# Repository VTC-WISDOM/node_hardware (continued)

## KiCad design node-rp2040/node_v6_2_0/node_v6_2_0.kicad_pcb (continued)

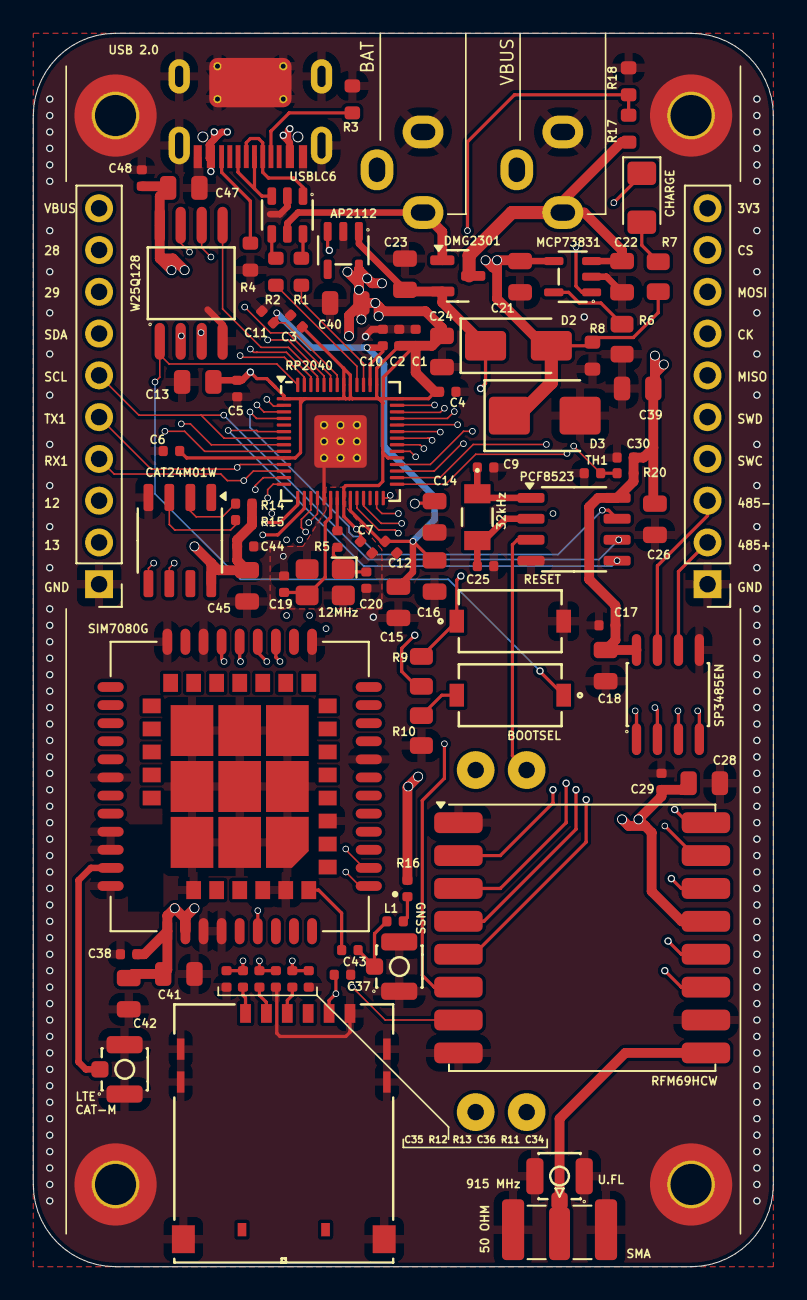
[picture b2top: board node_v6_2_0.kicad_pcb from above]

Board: 6 copper layers, 45.0 x 75.0 mm, 96 parts (1 on the bottom side), 77 nets.

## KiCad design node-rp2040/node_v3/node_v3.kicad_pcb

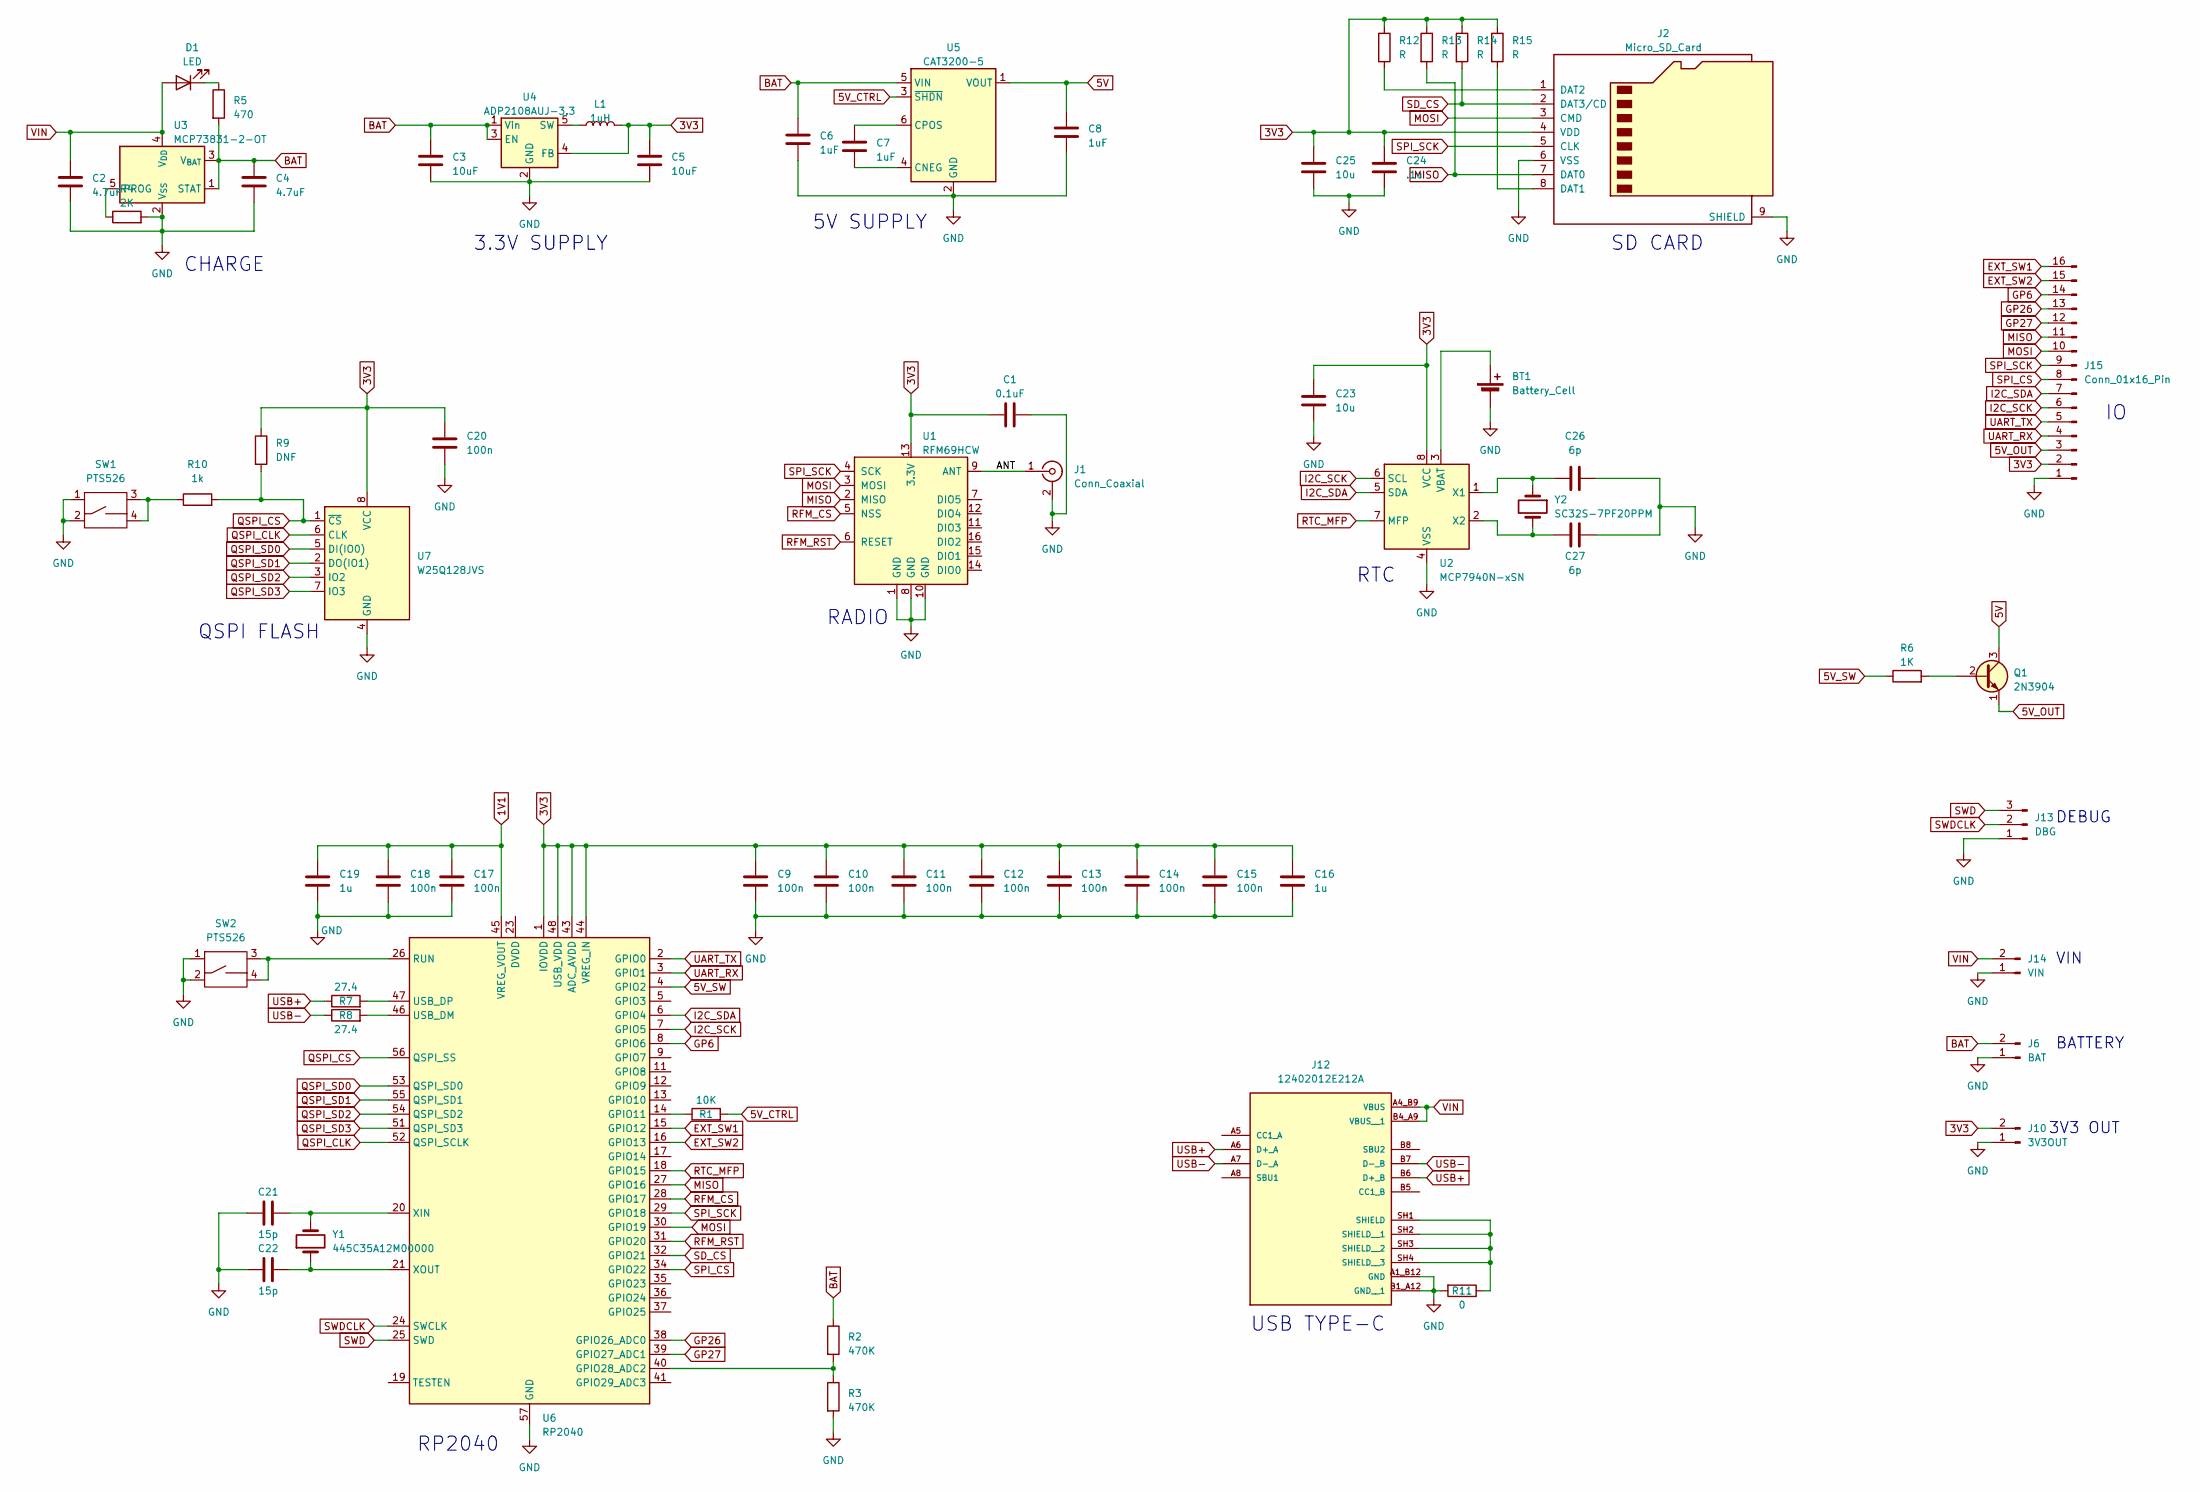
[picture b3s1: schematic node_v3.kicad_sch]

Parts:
BT1: Battery_Cell; BAT-HLD-001-THM_TEC
C1: 0.1uF; C_0402_1005Metric
C2, C4: 4.7uF; C_0805_2012Metric_Pad1.18x1.45mm_HandSolder
C3, C5: 10uF; C_0805_2012Metric_Pad1.18x1.45mm_HandSolder
C6, C7, C8: 1uF; C_0805_2012Metric_Pad1.18x1.45mm_HandSolder
C9, C10, C11, C12, C13, C14, C15, C17, C18, C20: 100n; C_0402_1005Metric_Pad0.74x0.62mm_HandSolder
C16, C19: 1u; C_0805_2012Metric_Pad1.18x1.45mm_HandSolder
C21, C22: 15p; C_0402_1005Metric_Pad0.74x0.62mm_HandSolder
C23, C25: 10u; C_0805_2012Metric_Pad1.18x1.45mm_HandSolder
C24: .1u; C_0402_1005Metric
C26, C27: 6p; C_0603_1608Metric_Pad1.08x0.95mm_HandSolder
D1: LED; LED_1206_3216Metric_Pad1.42x1.75mm_HandSolder
J1: Conn_Coaxial; SMA_Samtec_SMA-J-P-X-ST-EM1_EdgeMount
J2: Micro_SD_Card; microSD_HC_Molex_104031-0811
J6: BAT; PinHeader_1x02_P2.54mm_Vertical
J10: 3V3OUT; PinHeader_1x02_P2.54mm_Vertical
J12: 12402012E212A; AMPHENOL_12402012E212A; PARTREV 4
J13: DBG; PinHeader_1x03_P2.54mm_Vertical
J14: VIN; PinHeader_1x02_P2.54mm_Vertical
J15: Conn_01x16_Pin; PinHeader_1x16_P2.54mm_Vertical
L1: 1uH; L_1008_2520Metric_Pad1.43x2.20mm_HandSolder
Q1: 2N3904; SC-59_Handsoldering
R1: 10K; R_0805_2012Metric_Pad1.20x1.40mm_HandSolder
R2, R3: 470K; R_0805_2012Metric_Pad1.20x1.40mm_HandSolder
R4: 2K; R_0805_2012Metric_Pad1.20x1.40mm_HandSolder
R5: 470; R_0805_2012Metric_Pad1.20x1.40mm_HandSolder
R6: 1K; R_0805_2012Metric_Pad1.20x1.40mm_HandSolder
R7, R8: 27.4; R_0805_2012Metric_Pad1.20x1.40mm_HandSolder
R9: DNF; R_0805_2012Metric_Pad1.20x1.40mm_HandSolder
R10: 1k; R_0805_2012Metric_Pad1.20x1.40mm_HandSolder
R11: 0; R_0805_2012Metric_Pad1.20x1.40mm_HandSolder
R12, R13, R14, R15: R; R_0805_2012Metric_Pad1.20x1.40mm_HandSolder
SW1, SW2: PTS526
U1: RFM69HCW; HOPERF_RFM9XW_SMD
U2: MCP7940N-xSN; SOIC-8_3.9x4.9mm_P1.27mm
U3: MCP73831-2-OT; SOT-23-5
U4: ADP2108AUJ-3.3; TSOT-23-5
U5: CAT3200-5; SOT-23-6
U6: RP2040; QFN-56-1EP_7x7mm_P0.4mm_EP3.2x3.2mm
U7: W25Q128JVS; SOIC-8_5.23x5.23mm_P1.27mm
Y1: 445C35A12M00000; XTAL_M445
Y2: SC32S-7PF20PPM; SC-32S

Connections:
1V1: C17.1, C18.1, C19.1, U6.45 (VREG_VOUT)
3V3: C1.1, C5.1, C9.1, C10.1, C11.1, C12.1, C13.1, C14.1, C15.1, C16.1, C20.1, C23.1, C24.1, C25.1, J2.4 (VDD), J10.2, J15.2, L1.2, R9.1, R12.1, R13.1, R14.1, R15.1, U1.13 (3.3V), U2.8 (VCC), U4.4 (FB), U6.1 (IOVDD), U6.10 (IOVDD), U6.22 (IOVDD), U6.33 (IOVDD), U6.42 (IOVDD), U6.43 (ADC_AVDD), U6.44 (VREG_IN), U6.48 (USB_VDD), U6.49 (IOVDD), U7.8 (VCC)
5V: C8.1, Q1.3 (C), U5.1 (VOUT)
5V_CTRL: R1.2, U5.3 (~SHDN)
5V_OUT: J15.3, Q1.1 (E)
5V_SW: R6.1, U6.4 (GPIO2)
/ANT: J1.1 (In), U1.9 (ANT)
BAT: C3.1, C4.1, C6.1, J6.2, R2.1, R5.2, U3.1 (STAT), U3.3 (V_{BAT}), U4.1 (Vin), U4.3 (EN), U5.5 (VIN)
EXT_SW1: J15.16, U6.15 (GPIO12)
EXT_SW2: J15.15, U6.16 (GPIO13)
GP6: J15.14, U6.8 (GPIO6)
GP26: J15.13, U6.38 (GPIO26_ADC0)
GP27: J15.12, U6.39 (GPIO27_ADC1)
I2C_SCK: J15.6, U2.6 (SCL), U6.7 (GPIO5)
I2C_SDA: J15.7, U2.5 (SDA), U6.6 (GPIO4)
MISO: J2.7 (DAT0), J15.11, R13.2, U1.2 (MISO), U6.27 (GPIO16)
MOSI: J2.3 (CMD), J15.10, U1.3 (MOSI), U6.30 (GPIO19)
unnamed: D1.1 (K), R5.1
unnamed: J2.8 (DAT1), R15.2
unnamed: J2.1 (DAT2), R12.2
unnamed: J12.SH1 (SHIELD), J12.SH2 (SHIELD__1), J12.SH3 (SHIELD__2), J12.SH4 (SHIELD__3), R11.1
unnamed: Q1.2 (B), R6.2
unnamed: R10.1, SW1.3, SW1.4
unnamed: C26.1, U2.1 (X1), Y2.1
unnamed: C27.1, U2.2 (X2), Y2.2
unnamed: R4.1, U3.5 (PROG)
unnamed: L1.1, U4.5 (SW)
unnamed: C7.2, U5.4 (CNEG)
unnamed: C7.1, U5.6 (CPOS)
unnamed: U6.23 (DVDD), U6.50 (DVDD)
unnamed: R1.1, U6.14 (GPIO11)
unnamed: R2.2, R3.1, U6.40 (GPIO28_ADC2)
unnamed: SW2.3, SW2.4, U6.26 (RUN)
unnamed: R8.2, U6.46 (USB_DM)
unnamed: R7.2, U6.47 (USB_DP)
unnamed: C21.2, U6.20 (XIN), Y1.2
unnamed: C22.2, U6.21 (XOUT), Y1.1
QSPI_CLK: U6.52 (QSPI_SCLK), U7.6 (CLK)
QSPI_CS: R9.2, R10.2, U6.56 (QSPI_SS), U7.1 (~CS)
QSPI_SD0: U6.53 (QSPI_SD0), U7.5 (DI(IO0))
QSPI_SD1: U6.55 (QSPI_SD1), U7.2 (DO(IO1))
QSPI_SD2: U6.54 (QSPI_SD2), U7.3 (IO2)
QSPI_SD3: U6.51 (QSPI_SD3), U7.7 (IO3)
RFM_CS: U1.5 (NSS), U6.28 (GPIO17)
RFM_RST: U1.6 (RESET), U6.31 (GPIO20)
RTC_MFP: U2.7 (MFP), U6.18 (GPIO15)
SD_CS: J2.2 (DAT3/CD), R14.2, U6.32 (GPIO21)
SPI_CS: J15.8, U6.34 (GPIO22)
SPI_SCK: J2.5 (CLK), J15.9, U1.4 (SCK), U6.29 (GPIO18)
SWD: J13.3, U6.25 (SWD)
SWDCLK: J13.2, U6.24 (SWCLK)
UART_RX: J15.4, U6.3 (GPIO1)
UART_TX: J15.5, U6.2 (GPIO0)
USB+: J12.A6 (D+_A), J12.B6 (D+_B), R7.1
USB-: J12.A7 (D-_A), J12.B7 (D-_B), R8.1
VIN: C2.1, D1.2 (A), J12.A4_B9 (VBUS), J12.B4_A9 (VBUS__1), J14.2, U3.4 (V_{DD})

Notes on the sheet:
RTC
DEBUG
3V3 OUT
USB TYPE-C
3.3V SUPPLY
SD CARD
RADIO
RP2040
CHARGE
BATTERY
QSPI FLASH
VIN
5V SUPPLY

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
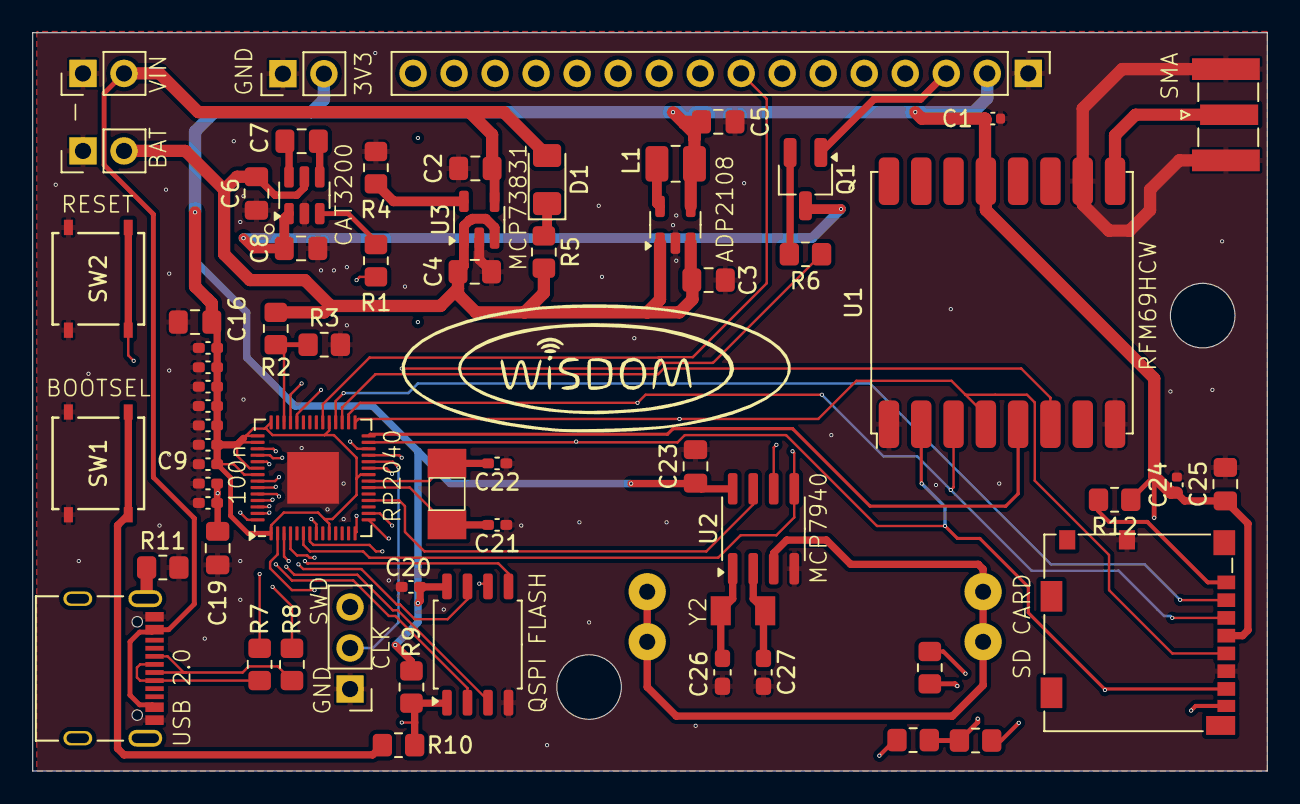
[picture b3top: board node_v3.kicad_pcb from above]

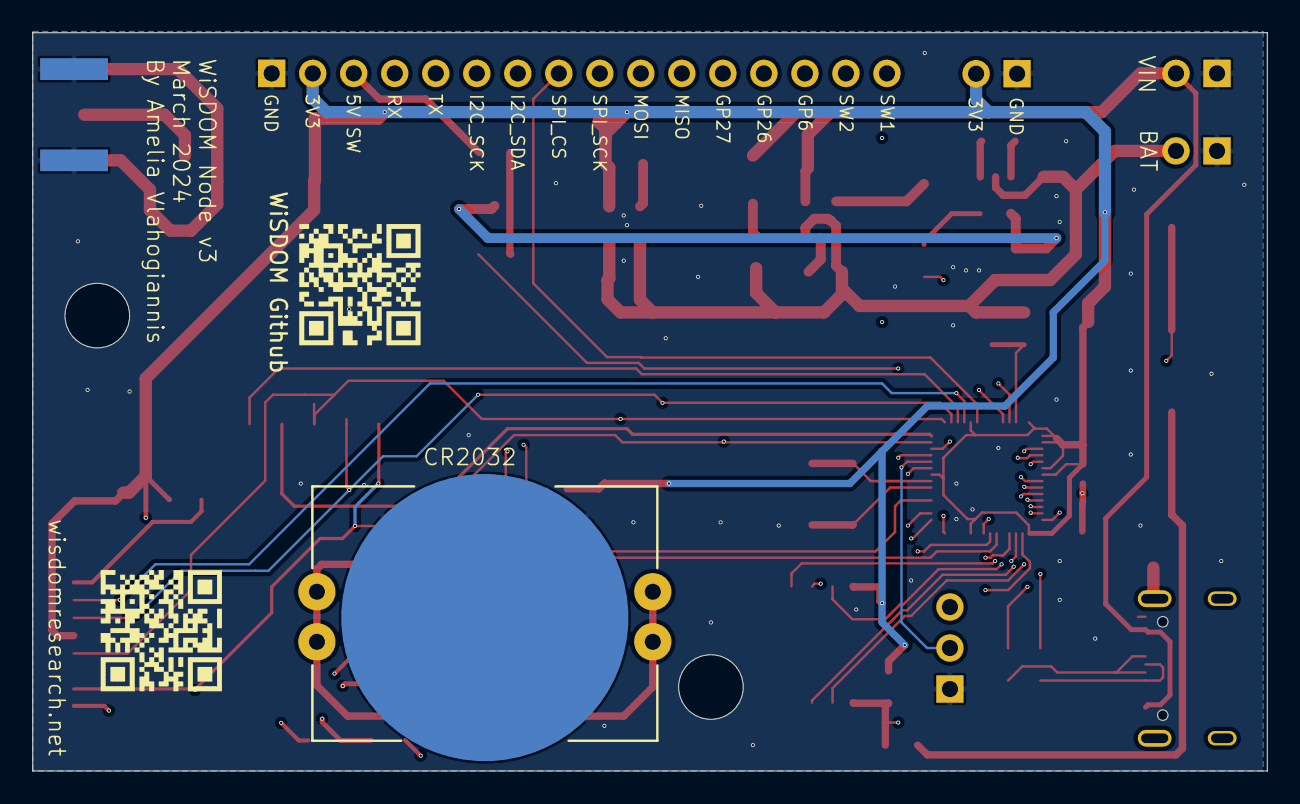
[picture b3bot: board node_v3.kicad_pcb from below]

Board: 4 copper layers, 76.5 x 45.7 mm, 67 parts (3 on the bottom side), 58 nets.

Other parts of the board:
LOGO: qrcode
LOGO#2: github_qr

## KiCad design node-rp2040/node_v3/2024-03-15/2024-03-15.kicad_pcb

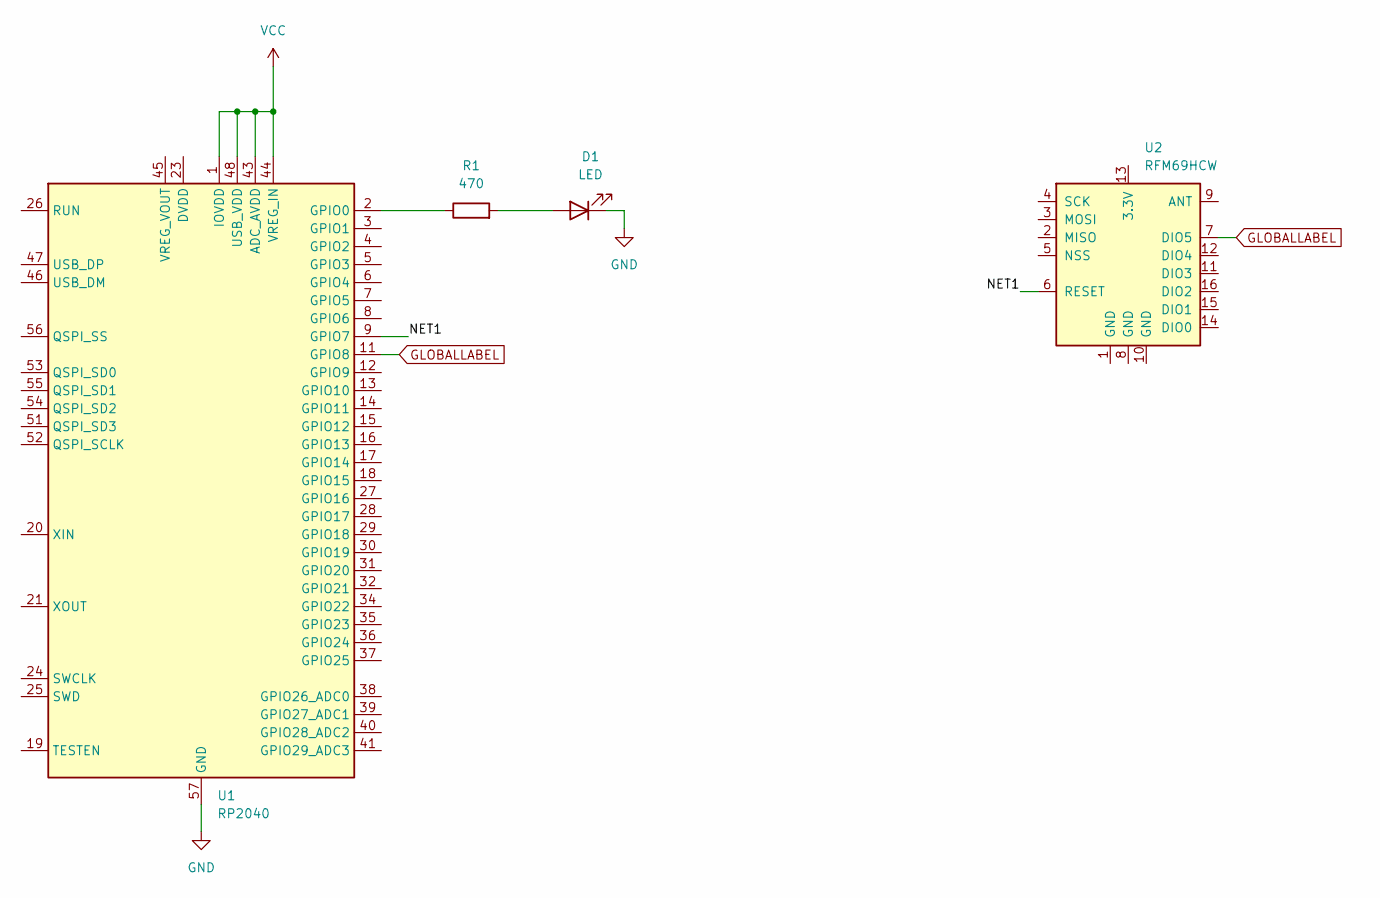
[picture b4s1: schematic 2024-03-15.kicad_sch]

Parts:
D1: LED; LED_D5.0mm
R1: 470; R_Axial_DIN0207_L6.3mm_D2.5mm_P7.62mm_Horizontal
U1: RP2040; QFN-56-1EP_7x7mm_P0.4mm_EP3.2x3.2mm
U2: RFM69HCW; HOPERF_RFM9XW_SMD

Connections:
/NET1: U1.9 (GPIO7), U2.6 (RESET)
GLOBALLABEL: U1.11 (GPIO8), U2.7 (DIO5)
GND: D1.1 (K), U1.57 (GND)
unnamed: D1.2 (A), R1.2
unnamed: U1.23 (DVDD), U1.50 (DVDD)
unnamed: R1.1, U1.2 (GPIO0)
VCC: U1.1 (IOVDD), U1.10 (IOVDD), U1.22 (IOVDD), U1.33 (IOVDD), U1.42 (IOVDD), U1.43 (ADC_AVDD), U1.44 (VREG_IN), U1.48 (USB_VDD), U1.49 (IOVDD)

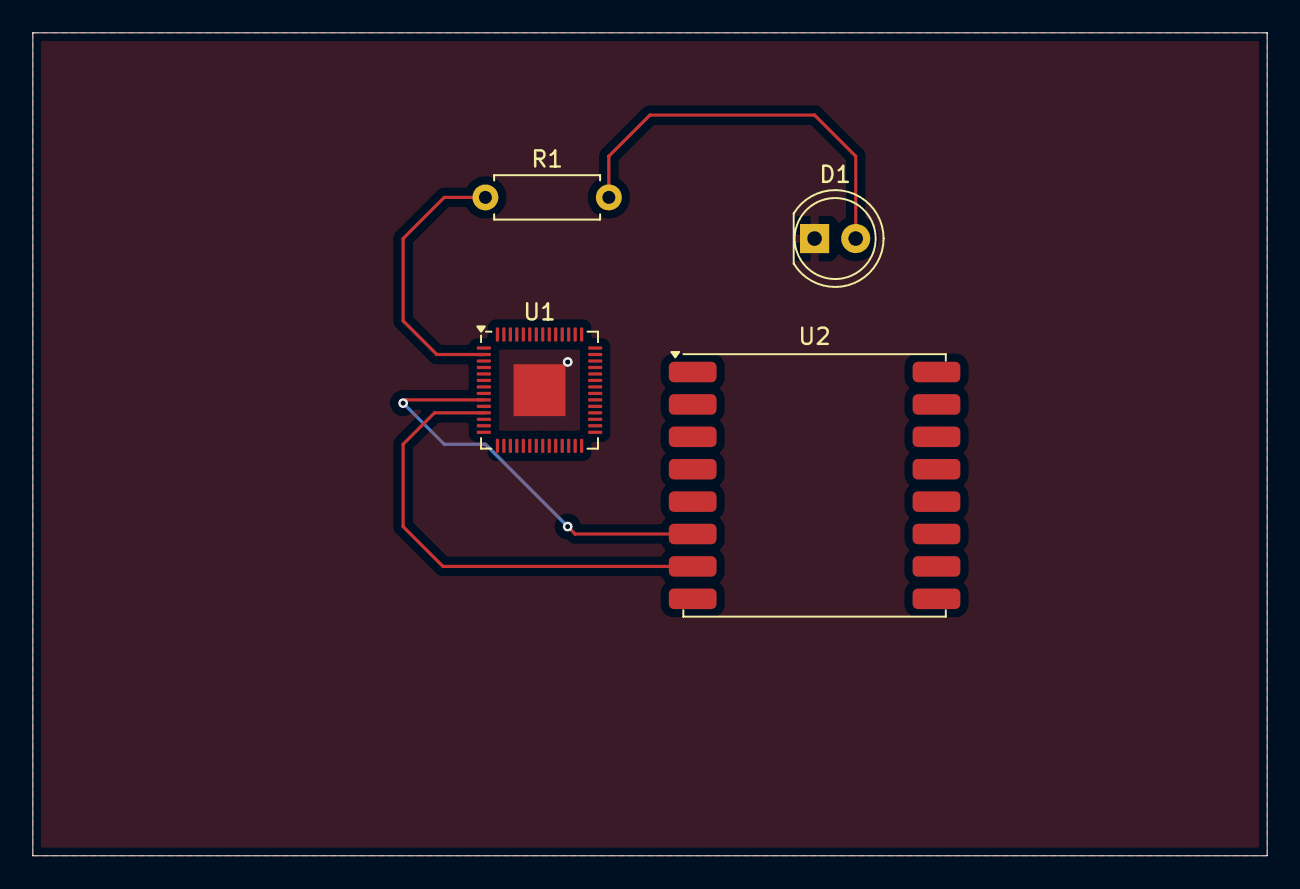
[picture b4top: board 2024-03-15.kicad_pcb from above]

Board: 2 copper layers, 76.2 x 50.8 mm, 4 parts (0 on the bottom side), 7 nets.

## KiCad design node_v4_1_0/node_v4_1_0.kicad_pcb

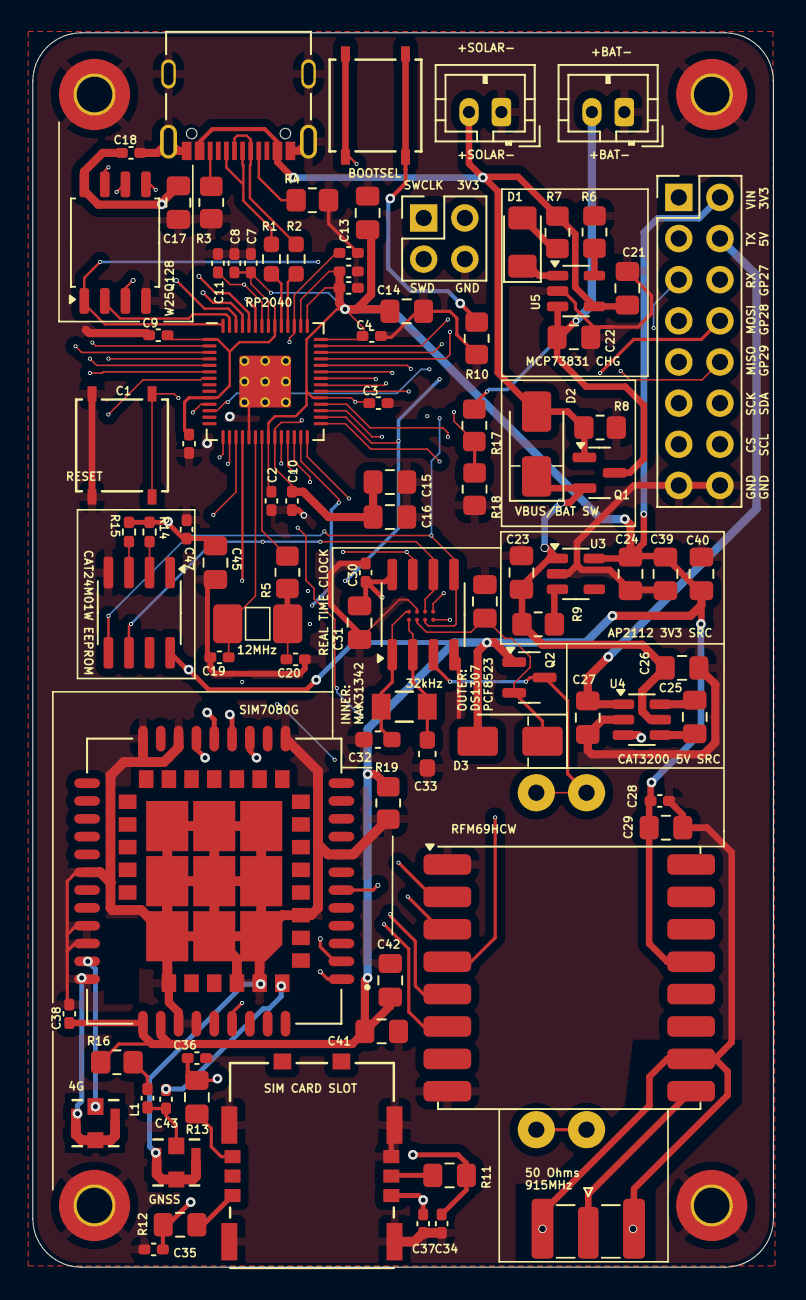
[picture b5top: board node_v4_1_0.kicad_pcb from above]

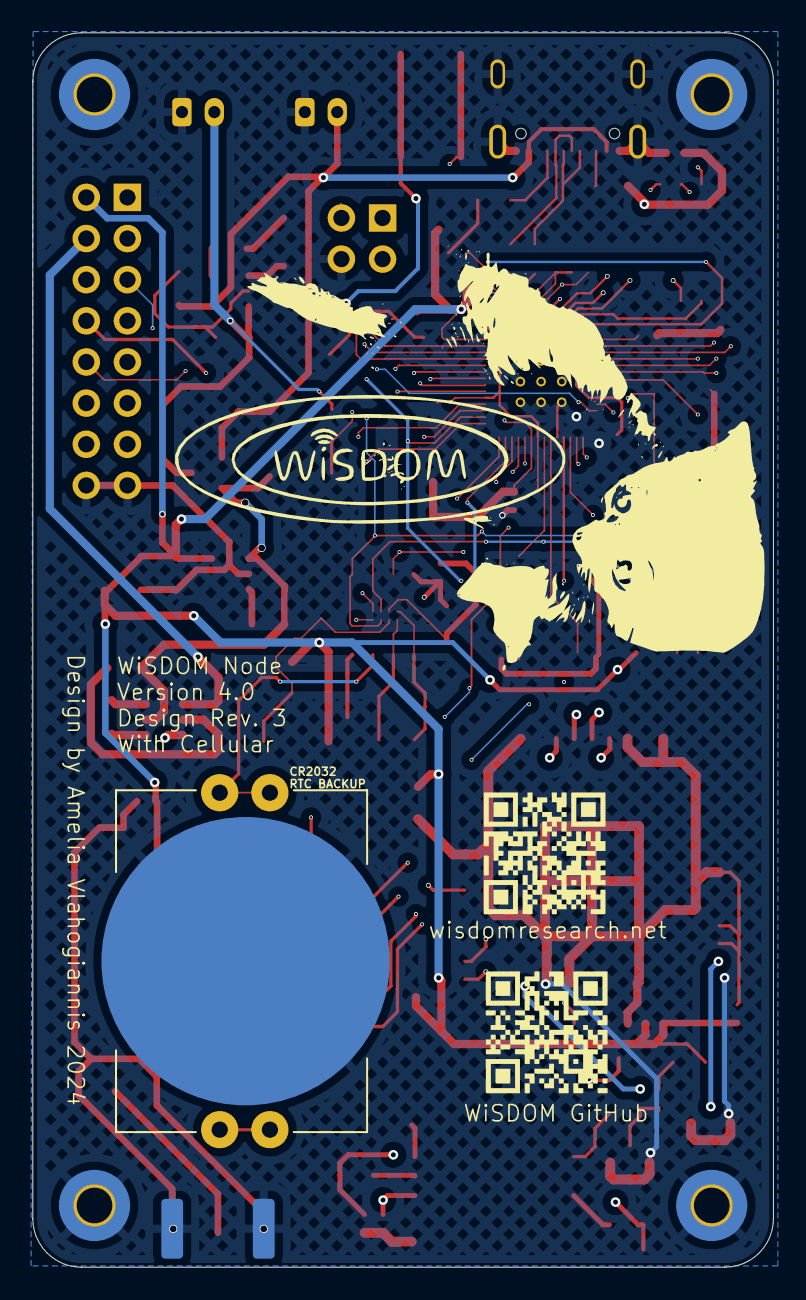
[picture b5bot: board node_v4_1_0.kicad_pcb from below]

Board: 4 copper layers, 45.7 x 76.2 mm, 101 parts (3 on the bottom side), 71 nets.

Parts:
BT1: RTC_BAT; BAT_BAT-HLD-001-THM
C1, C2, C3, C4, C5, C6, C7, C8, C9, C10, C11, C12, C18, C28, C30, C37, C38, C44: 0.1u; C_0402_1005Metric_Pad0.74x0.62mm_HandSolder
C13, C15, C17, C23, C24, C29, C31, C45, C46: 10u; C_0805_2012Metric_Pad1.18x1.45mm_HandSolder
C14, C16, C25, C26, C27, C41: 1u; C_0805_2012Metric_Pad1.18x1.45mm_HandSolder
C19, C20: 15pF; C_0402_1005Metric_Pad0.74x0.62mm_HandSolder
C21, C22: 4.7u; C_0805_2012Metric_Pad1.18x1.45mm_HandSolder
C32, C33: 6p; C_0603_1608Metric_Pad1.08x0.95mm_HandSolder
C34, C35, C36, C43: 33p; C_0402_1005Metric_Pad0.74x0.62mm_HandSolder
C39, C40, C42: 100u; C_0805_2012Metric_Pad1.18x1.45mm_HandSolder
D1: LED; LED_1206_3216Metric_Pad1.42x1.75mm_HandSolder
D2, D3: SS14; D_SMA
H1, H2, H3, H4: MountingHole_Pad; MountingHole_2.2mm_M2_Pad_TopBottom
J1, J8: Conn_01x02_Pin; JST_PH_B2B-PH-K_1x02_P2.00mm_Vertical
J2: 12402012E212A; AMPHENOL_12402012E212A
J3: Conn_Coaxial; SMA_Samtec_SMA-J-P-H-ST-EM1_EdgeMount
J4: Conn_02x08_Odd_Even; PinHeader_2x08_P2.54mm_Vertical
J5: Conn_02x02_Odd_Even; PinHeader_2x02_P2.54mm_Vertical
J6: GNSS_ANT; CONN_CONMHF1-SMD_LNX
J7: RF_ANT; CONN_CONMHF1-SMD_LNX
L1: L; L_0402_1005Metric_Pad0.77x0.64mm_HandSolder
LOGO: qrcode
LOGO#2: github_qr
Q1, Q2: DMG2301L; SOT-23
R1, R2: 27.4; R_0603_1608Metric_Pad0.98x0.95mm_HandSolder
R3, R4: 5.1k; R_0805_2012Metric_Pad1.20x1.40mm_HandSolder
R5, R7: 1k; R_0805_2012Metric_Pad1.20x1.40mm_HandSolder
R6: 2k; R_0805_2012Metric_Pad1.20x1.40mm_HandSolder
R8, R10, R19: 10k; R_0805_2012Metric_Pad1.20x1.40mm_HandSolder
R9: R; R_0805_2012Metric_Pad1.20x1.40mm_HandSolder
R11, R12, R13: 22; C_0805_2012Metric_Pad1.18x1.45mm_HandSolder
R14, R15: 10k DNF; R_0402_1005Metric_Pad0.72x0.64mm_HandSolder
R16: 22; R_0805_2012Metric_Pad1.20x1.40mm_HandSolder
R17, R18: 470k; R_0805_2012Metric_Pad1.20x1.40mm_HandSolder
U1: RP2040; RP2040-QFN-56
U2: W25Q128JVS; SOIC-8_5.23x5.23mm_P1.27mm
U3: AP2112K-3.3; SOT-23-5
U4: CAT3200-5; SOT-23-6
U5: MCP73831-2-OT; SOT-23-5
U6: RFM69HCW; HOPERF_RFM9XW_SMD
U7, U8: PTS526 SK15 SMTR2 LFS; PTS526
U9: SIM7080G; XCVR_SIM7080G
U10: MCP7940 / DS1307 / PCF8523; SOIC-8_3.9x4.9mm_P1.27mm
U11: 1042240820; 1042240820_MOL
U12: CAT24M01W; SOIC-8_3.9x4.9mm_P1.27mm
U13: MAX31342EWA+T; 21-100291_W80D&plus_1_MXM
X1: XTAL-445
XTAL1: SC32S-7PF20PPM; XTAL_SC32S-7PF20PPM_EPS

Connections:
5V_CTRL: U1.16 (GPIO13), U4.3 (~SHDN)
+1V1: C10.1, C11.1, C12.1, C15.1, C16.1, U1.23 (DVDD), U1.45 (VREG_VOUT), U1.50 (DVDD)
+3.3V: C1.1, C2.1, C3.1, C4.1, C5.1, C6.1, C7.1, C8.1, C9.1, C13.1, C14.1, C17.1, C18.1, C24.1, C28.1, C29.1, C30.1, C31.1, C38.1, C39.1, C40.1, C41.1, C42.1, C44.1, C45.1, D3.2 (A), J4.2, J5.2, Q2.1 (G), R14.1, R15.1, R16.1, R19.1, U1.1 (IOVDD), U1.10 (IOVDD), U1.22 (IOVDD), U1.33 (IOVDD), U1.42 (IOVDD), U1.43 (ADC_AVDD), U1.44 (VREG_IN), U1.48 (USB_VDD), U1.49 (IOVDD), U2.8 (VCC), U3.5 (VOUT), U6.13 (3.3V), U9.34 (VBAT), U9.35 (VBAT__1), U10.8 (VCC), U12.8 (VCC)
+5V: C27.1, J4.4, U4.1 (VOUT)
+BATT: C22.1, J1.2, Q1.3 (D), R17.1, U5.3 (V_{BAT})
+VRTC: C46.1, D3.1 (K), Q2.2 (S), U13.B2 (VCC)
+VSW: C23.1, C26.1, D2.1 (K), Q1.2 (S), R9.1, U3.1 (VIN), U4.5 (VIN)
/MCU/CLK: U1.52 (QSPI_SCLK), U2.6 (CLK)
/MCU/CS: U1.56 (QSPI_SS), U2.1 (~CS), U8.1, U8.2
/MCU/D0: U1.53 (QSPI_SD0), U2.5 (DI(IO0))
/MCU/D1: U1.55 (QSPI_SD1), U2.2 (DO(IO1))
/MCU/D2: U1.54 (QSPI_SD2), U2.3 (IO2)
/MCU/D3: U1.51 (QSPI_SD3), U2.7 (IO3)
/MCU/RESET: U1.26 (RUN), U7.1, U7.2
/MCU/XTAL+: C19.1, U1.20 (XIN), X1.2
/MCU/XTAL-: R5.1, U1.21 (XOUT)
/PERIPHERALS/ANT: J3.1 (In), U6.9 (ANT)
/PERIPHERALS/RTC_X1: C32.1, U10.1 (X1), U13.A1 (X2), XTAL1.1
/PERIPHERALS/RTC_X2: C33.1, U10.2 (X2), U13.B1 (X1), XTAL1.2
/PERIPHERALS/SIM_CLK: C35.1, R12.1, U9.16 (SIM_CLK)
/PERIPHERALS/SIM_IO: C36.1, R13.1, U9.15 (SIM_DATA)
/PERIPHERALS/SIM_RST: C34.1, R11.1, U9.17 (SIM_RST)
/PERIPHERALS/SIM_VCC: C37.1, U9.18 (SIM_VDD), U11.S1 (VCC)
GND: BT1.2 (-), C1.2, C2.2, C3.2, C4.2, C5.2, C6.2, C7.2, C8.2, C9.2, C10.2, C11.2, C12.2, C13.2, C14.2, C15.2, C16.2, C17.2, C18.2, C19.2, C20.2, C21.2, C22.2, C23.2, C24.2, C26.2, C27.2, C28.2, C29.2, C30.2, C31.2, C32.2, C33.2, C34.2, C35.2, C36.2, C37.2, C38.2, C39.2, C40.2, C41.2, C42.2, C44.2, C45.2, C46.2, H1.1, H2.1, H3.1, H4.1, J1.1, J2.A1_B12 (GND), J2.B1_A12 (GND__1), J2.SH1 (SHIELD), J2.SH2 (SHIELD__1), J2.SH3 (SHIELD__2), J2.SH4 (SHIELD__3), J3.2 (Ext), J4.15, J4.16, J5.4, J6.2 (Ext), J7.2 (Ext), J8.1, R3.2, R4.2, R6.2, R8.2, R10.2, R18.2, R19.2, U1.19 (TESTEN), U1.57 (GND), U2.4 (GND), U3.2 (GND), U4.2 (GND), U5.2 (V_{SS}), U6.1 (GND), U6.8 (GND), U6.10 (GND), U7.3, U7.4, U9.8 (GND), U9.13 (GND__1), U9.19 (GND__2), U9.21 (GND__3), U9.27 (GND__4), U9.30 (GND__5), U9.31 (GND__6), U9.33 (GND__7), U9.36 (GND__8), U9.37 (GND__9), U9.45 (GND__10), U9.63 (GND__11), U9.66 (GND__12), U9.67 (GND__13), U9.69 (GND__14), U9.70 (GND__15), U9.71 (GND__16), U9.72 (GND__17), U9.73 (GND__18), U9.74 (GND__19), U9.75 (GND__20), U9.76 (GND__21), U9.77 (GND__22), U10.4 (VSS), U11.G1 (GND), U11.G2 (GND), U11.G3 (GND), U11.G4 (GND), U11.S4 (GND), U12.4 (GND), U13.A2 (GND)
GNSS_ANT: C43.1, U9.68 (GNSS_ANT)
GP27: J4.6, U1.39 (GPIO27_ADC1)
GP28: J4.8, U1.40 (GPIO28_ADC2)
GP29: J4.10, U1.41 (GPIO29_ADC3)
MISO: J4.9, U1.27 (GPIO16), U6.2 (MISO)
MOSI: J4.7, U1.30 (GPIO19), U6.3 (MOSI)
unnamed: C20.1, R5.2, X1.1
unnamed: D1.2 (A), R7.1
unnamed: D1.1 (K), U5.1 (STAT)
unnamed: J2.A5 (CC1_A), R4.1
unnamed: J2.B5 (CC1_B), R3.1
unnamed: C43.2, J6.1 (In), L1.2
unnamed: L1.1, R16.2
unnamed: R10.1, U8.3, U8.4
unnamed: R2.1, U1.46 (USB_DM)
unnamed: R1.1, U1.47 (USB_DP)
unnamed: R9.2, U3.3 (EN)
unnamed: C25.2, U4.4 (CNEG)
unnamed: C25.1, U4.6 (CPOS)
unnamed: R6.1, U5.5 (PROG)
unnamed: R12.2, U11.S3 (CLK)
unnamed: R13.2, U11.S6 (I/O)
unnamed: R11.2, U11.S2 (RST)
unnamed: R14.2, U12.2 (A1)
unnamed: R15.2, U12.3 (A2)
PWRKEY: U1.17 (GPIO14), U9.39 (PWRKEY)
RFM_CS: U1.28 (GPIO17), U6.5 (NSS)
RFM_RST: U1.31 (GPIO20), U6.6 (RESET)
RF_ANT: J7.1 (In), U9.32 (RF_ANT)
RTC_BAT: BT1.1 (+), Q2.3 (D), U10.3 (VBAT)
RTC_MFP1: U1.4 (GPIO2), U10.7 (MFP), U13.B4 (INTA)
RTC_MFP2: U1.5 (GPIO3), U13.A4 (INTB)
RX0: U1.3 (GPIO1), U9.1 (UART1_TXD)
RX1: J4.5, U1.12 (GPIO9)
SCL: J4.14, U1.7 (GPIO5), U10.6 (SCL), U12.6 (SCL), U13.A3 (SCL)
SDA: J4.12, U1.6 (GPIO4), U10.5 (SDA), U12.5 (SDA), U13.B3 (SDA)
SIM_DTR: U1.18 (GPIO15), U9.6 (UART1_DTR)
SPI_CK: J4.11, U1.29 (GPIO18), U6.4 (SCK)
SPI_CS: J4.13, U1.32 (GPIO21)
SWCLK: J5.1, U1.24 (SWCLK)
SWD: J5.3, U1.25 (SWD)
TX0: U1.2 (GPIO0), U9.2 (UART1_RXD)
TX1: J4.3, U1.11 (GPIO8)
USB+: J2.A6 (D+_A), J2.B6 (D+_B), R1.2
USB-: J2.A7 (D-_A), J2.B7 (D-_B), R2.2
VBAT_SAMPLE: R17.2, R18.1, U1.38 (GPIO26_ADC0)
VBUS: C21.1, D2.2 (A), J2.A4_B9 (VBUS), J2.B4_A9 (VBUS__1), J4.1, J8.2, Q1.1 (G), R7.2, R8.1, U5.4 (V_{DD})

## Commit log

2024-01-19 added all the stuff!
2024-01-19 readme
2024-01-26 created new kicad project, moved v1 schematic over for modifications, added todo list
2024-03-02 v1 should be organized and complete and up to date. v2 was lost in an rm accident
2024-03-02 created v3 project, imported v1 schematic to be majorly updated
2024-03-02 added missing grounds
2024-03-08 replaced pico with rp2040
2024-03-19 progress
2024-03-23 moved stuff around, replaced headers, usb, footprints, started pcb
2024-03-24 finished? the pcb design - need to look into sd card stuff first
2024-03-25 not finished yet
2024-03-31 fixed the rfm footprint, fixed via sizes. need to adjust some vias to be bigger
2024-04-03 minor trace changes
2024-04-11 finalized pcb v3, added silkscreen and all and fixed some issues found in the drc
2024-04-12 actually saved work this time
2024-05-25 v3.1 begin
2024-05-27 minor adjustments
2024-05-28 started pcb
2024-05-28 finished layout(probably)
2024-06-04 ready to order(probably)
2024-06-10 created kicad drawings
2024-06-10 lock files or something
2024-06-10 minor
2024-07-30 begin v4
2024-07-30 converted v4 to different format and started the schematic(from scratch again)
2024-08-10 more tracing, added RFM, added SIM, built power systems. converted to star ground
2024-08-13 lots of stuff
2024-08-13 placed everything in the sim version
2024-08-13 added footprint
2024-08-13 so much
2024-08-13 placed power supplies
2024-08-13 finished laying out the board
2024-08-14 most routing done
2024-08-14 done!
2024-08-15 added vin for solar/charge, more minor fixes
2024-08-15 moved reset button to make space for vin jst connector
2024-08-20 extended pads on RP2040 footprint for easier soldering by hand
2024-08-20 renamed directories for proper organization, updated readme
2024-08-20 renamed more directories and files
2024-08-20 add CERN weakly reciprocal license
2024-08-20 remove kicad-libs to put them in their own repository
2024-08-20 add submodule
2024-08-25 updated to v4.1.0 - separate uart0 and 1 for SIM7080G / pinouts, add PWRKEY pin, add 5v control line, replace 32khz crystal caps with 0603. minor adjustments to component placement.
2024-09-23 small changes to 4.1.1 routing
2024-12-27 added submodule
2025-01-03 created v5, started changing parts over to JLC preferred
2025-01-08 updated layout
2025-01-08 lots of routing
2025-01-08 drc time
2025-01-08 weird submodule stuff i dont understand
2025-01-08 again
2025-01-08 finished layout and routing?
2025-01-09 updated layout of silkscreen, added labels and qr codes
2025-01-16 pinouts
2025-03-23 begin reworking library storage
2025-03-23 moved stuff around
2025-03-23 updating kicad-libs submodule stuff
2025-03-23 cleaning
2025-03-23 i think it works
2025-03-23 updated docs
2025-03-23 removed nodes prior to V5 and moved them to a separate repo for deprecated designs
2025-05-21 i should have made this more than one commit but: 1) started poking around in v5 to find and solve a sim card problem, forgot about it and moved on 2) created v6, modified the schematic somewhat, rem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
2025-05-23 finished initial routing
2025-05-23 added silkscreens, fixed missing caps on RP2040 XTAL
2025-05-23 moved SWD pads, confirmed DRC ok
2025-06-02 moved v6.0.1 to v6.1.0, which is cancelled, and laid out (most of) board for v6.2.0 + began routing
2025-06-03 finished layout v6.2
2025-06-03 finished routing; todo: labels and silkscreen, final review
2025-06-04 removed duplicated jlc lib
2025-06-04 submodules
2025-06-04 added zener diode for overvoltage protection on vbus, small routing adjustments, silkscreen component labels
2025-06-04 finish silkscreen and verification
2025-06-04 gitignore
2025-06-04 finished v6.2
2025-07-02 demo board
2025-07-02 update submodules
2026-01-12 move some stuff around
2026-03-06 update kicad libs
2026-03-31 analysis and notation of major components, power consumption, capacitor types, temperature tolerances
